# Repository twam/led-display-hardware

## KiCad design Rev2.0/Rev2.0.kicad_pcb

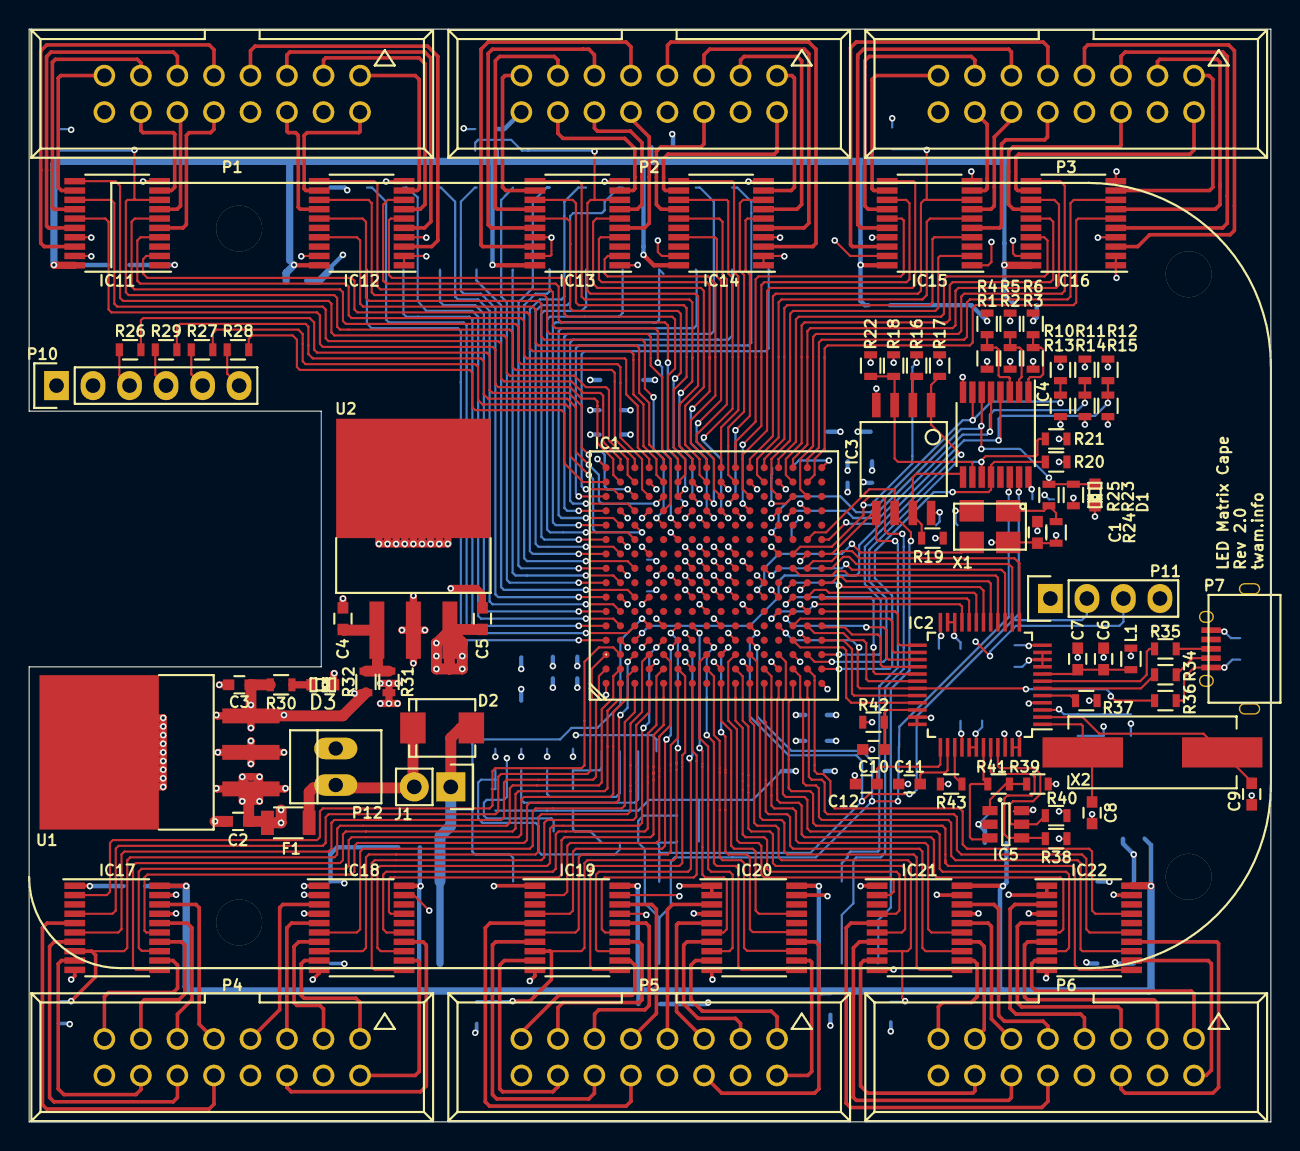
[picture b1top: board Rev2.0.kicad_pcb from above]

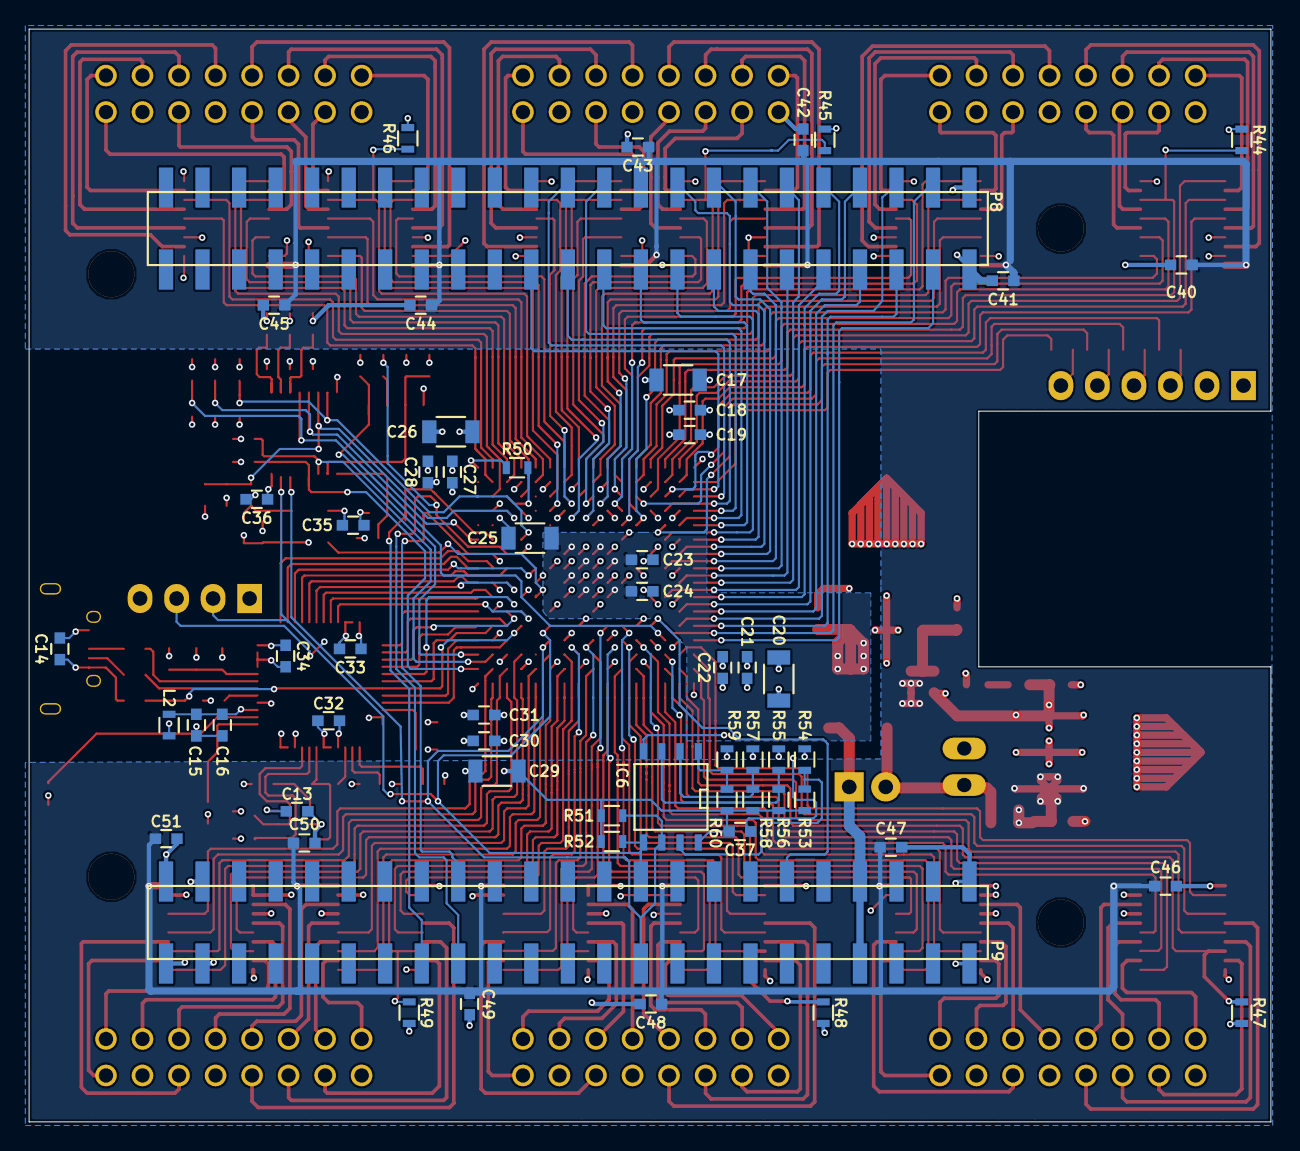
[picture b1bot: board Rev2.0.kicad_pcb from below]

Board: 4 copper layers, 86.4 x 76.0 mm, 150 parts (58 on the bottom side), 256 nets.

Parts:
C1, C10, C14: 10n; C_0603
C2, C3, C4, C5, C6, C15, C18, C21, C23, C27, C30: 4u7; C_0603
C7, C11, C12, C13, C16, C32, C33, C34, C35, C36, C37, C40, C41, C42, C43, C44, C45, C46, C47, C48, C49, C50, C51: 100n; C_0603
C8, C9: 27p; C_0603
C17, C20, C25, C26, C29: 100u; C_1206
C19, C22, C24, C28, C31: 470n; C_0603
D1, D3: LED; LED-0603
D2: DIODE; DO-214-AA
F1: FUSE; R_1206
IC1: XC6SLX25-FTG256; BGA-256
IC2: FT232H; LQFP-48_7x7mm_Pitch0.5mm
IC3: M25PE16; SO8W
IC4: PCA9534PW; TSSOP-16_4.4x5mm_Pitch0.65mm
IC5: 93LC56BT-I/OT; SOT-23-6
IC6: 24LC256; SOIC-8-N
IC11, IC12, IC13, IC14, IC15, IC16, IC17, IC18, IC19, IC20, IC21, IC22: SN74ACT244; TSSOP-20_4.4x6.5mm_Pitch0.65mm
J1: JUMPER-2; Pin_Header_Straight_1x02
L1, L2: 600R/0.5A; R_0603
MOUNTING_HOLE_3-2MM_M3, MOUNTING_HOLE_3-2MM_M3#2, MOUNTING_HOLE_3-2MM_M3#3, MOUNTING_HOLE_3-2MM_M3#4: VAL**; MOUNTING_HOLE_3-2MM_M3
P1, P2, P3, P4, P5, P6: CONN_02X08; VASCH8x2
P7: USB-MICRO-B; 47589-0001
P8: BEAGLEBONE_P8; PIN_HEADER_SMD_2x23
P9: BEAGLEBONE_P9; PIN_HEADER_SMD_2x23
P10: JTAG; Pin_Header_Straight_1x06
P11: I2C; Pin_Header_Straight_1x04
P12: POWER; PINHEAD1-2
R1, R2, R24, R38, R40: 10k N.F.; R_0603
R3: 10k N.F..; R_0603
R4, R5, R6, R10, R11, R12, R13, R14, R15, R17, R18, R19, R20, R21, R22, R25, R39, R42, R44, R45, R46, R47, R48, R49, R50, R53, R54, R55, R56, R57, R58, R59, R60: 10k; R_0603
R16, R26, R27, R28, R29: 100R; R_0603
R23, R30: 330R; R_0603
R31, R34, R35, R43: 0R; R_0603
R32: 0R N.F.; R_0603
R36: 39k; R_0603
R37: 12k/1%; R_0603
R41: 2k; R_0603
R51, R52: 4k7; R_0603
U1: MCP1826S-33; 3-DDPAK
U2: MCP1826S-12; 3-DDPAK
X1: ASFL1
X2: 12M; Crystal_HC49-SD_SMD

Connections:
+1.2V: C5.1, C23.1, C24.1, C25.1, IC1.G7, IC1.G9, IC1.H8, IC1.H10, IC1.J7, IC1.J9, IC1.K8, IC1.K10, U2.3
+3V3: C1.1, C3.1, C13.1, C17.1, C18.1, C19.1, C20.1, C21.1, C22.1, C26.1, C27.1, C28.1, C29.1, C30.1, C31.1, C32.1, C33.1, C34.1, C35.1, C36.1, C37.1, IC1.B4, IC1.B9, IC1.B13, IC1.D2, IC1.D7, IC1.D10, IC1.D15, IC1.E5, IC1.F8, IC1.F11, IC1.G4, IC1.G10, IC1.G13, IC1.H6, IC1.J2, IC1.J10, IC1.J15, IC1.K4, IC1.K13, IC1.L6, IC1.L9, IC1.N2, IC1.N7, IC1.N10, IC1.N15, IC1.R4, IC1.R8, IC1.R13, IC2.12, IC2.24, IC2.40, IC2.46, IC3.8, IC4.16, IC5.6, IC6.8, L1.2, L2.2, P10.1, P11.1, R1.1, R2.1, R3.1, R13.1, R14.1, R15.1, R17.1, R18.1, R19.1, R20.1, R21.1, R23.1, R24.1, R30.2, R32.2, R38.1, R39.1, R40.1, R42.2, R43.2, R44.2, R45.2, R46.2, R47.2, R48.2, R49.2, R51.1, R52.1, R53.1, R56.1, R58.1, R60.1, U1.3, X1.4
+5V: C2.1, C40.1, C41.1, C42.1, C43.1, C44.1, C45.1, C46.1, C47.1, C48.1, C49.1, C50.1, C51.1, F1.2, IC11.20, IC12.20, IC13.20, IC14.20, IC15.20, IC16.20, IC17.20, IC18.20, IC19.20, IC20.20, IC21.20, IC22.20, R31.2, U1.1
/BeagleBoneBlack/BBB_SYS_5V: D2.1, J1.1, P9.7, P9.8
/BeagleBoneBlack/GPMC_AD0: IC1.B14, P8.25
/BeagleBoneBlack/GPMC_AD1: IC1.A14, P8.24
/BeagleBoneBlack/GPMC_AD2: IC1.A5, P8.5
/BeagleBoneBlack/GPMC_AD3: IC1.B5, P8.6
/BeagleBoneBlack/GPMC_AD4: IC1.C13, P8.23
/BeagleBoneBlack/GPMC_AD5: IC1.A13, P8.22
/BeagleBoneBlack/GPMC_AD6: IC1.A4, P8.3
/BeagleBoneBlack/GPMC_AD7: IC1.C5, P8.4
/BeagleBoneBlack/GPMC_AD8: IC1.A12, P8.19
/BeagleBoneBlack/GPMC_AD9: IC1.C9, P8.13
/BeagleBoneBlack/GPMC_AD10: IC1.A9, P8.14
/BeagleBoneBlack/GPMC_AD11: IC1.C11, P8.17
/BeagleBoneBlack/GPMC_AD12: IC1.A8, P8.12
/BeagleBoneBlack/GPMC_AD13: IC1.B8, P8.11
/BeagleBoneBlack/GPMC_AD14: IC1.A10, P8.16
/BeagleBoneBlack/GPMC_AD15: IC1.A11, P8.15
/BeagleBoneBlack/GPMC_ADVN: IC1.A6, P8.7
/BeagleBoneBlack/GPMC_BE0N: IC1.C7, P8.9
/BeagleBoneBlack/GPMC_BE1N: IC1.D5, P9.12
/BeagleBoneBlack/GPMC_CLK: IC1.B10, P8.18
/BeagleBoneBlack/GPMC_CSN1: IC1.B12, P8.21
/BeagleBoneBlack/GPMC_OEN: IC1.B6, P8.8
/BeagleBoneBlack/GPMC_WE1N: IC1.A7, P8.10
/BeagleBoneBlack/I2C2_SCL: IC1.L4, IC4.14, IC6.6, P9.19, P11.3, R51.2
/BeagleBoneBlack/I2C2_SDA: IC1.L5, IC4.15, IC6.5, P9.20, P11.2, R52.2
/FPGA/A0_1: IC1.E15, IC11.2
/FPGA/A0_2: IC1.H16, IC13.2
/FPGA/A0_3: IC1.N14, IC15.2
/FPGA/A0_4: IC1.B3, IC17.2
/FPGA/A0_5: IC1.E3, IC19.2
/FPGA/A0_6: IC1.K3, IC21.2
/FPGA/A1_1: IC1.B15, IC11.15
/FPGA/A1_2: IC1.F14, IC13.15
/FPGA/A1_3: IC1.K16, IC15.15
/FPGA/A1_4: IC1.C3, IC17.15
/FPGA/A1_5: IC1.G1, IC19.15
/FPGA/A1_6: IC1.M2, IC21.15
/FPGA/A2_1: IC1.D16, IC11.4
/FPGA/A2_2: IC1.H13, IC13.4
/FPGA/A2_3: IC1.M16, IC15.4
/FPGA/A2_4: IC1.A3, IC17.4
/FPGA/A2_5: IC1.F4, IC19.4
/FPGA/A2_6: IC1.K1, IC21.4
/FPGA/A3_1: IC1.B16, IC11.13
/FPGA/A3_2: IC1.F15, IC13.13
/FPGA/A3_3: IC1.L13, IC15.13
/FPGA/A3_4: IC1.C2, IC17.13
/FPGA/A3_5: IC1.G3, IC19.13
/FPGA/A3_6: IC1.M1, IC21.13
/FPGA/ACBUS0: IC1.N6, IC2.21
/FPGA/ACBUS1: IC1.T6, IC2.25
/FPGA/ACBUS2: IC1.P5, IC2.26
/FPGA/ACBUS3: IC1.P6, IC2.27
/FPGA/ACBUS4: IC1.T5, IC2.28
/FPGA/ACBUS5: IC1.P7, IC2.29
/FPGA/ACBUS6: IC1.R5, IC2.30
/FPGA/ACBUS7: IC1.N5, IC2.31, R36.2
/FPGA/ACBUS8: IC1.T4, IC2.32
/FPGA/ACBUS9: IC1.P4, IC2.33
/FPGA/ADBUS0: IC1.R9, IC2.13
/FPGA/ADBUS1: IC1.T9, IC2.14
/FPGA/ADBUS2: IC1.M9, IC2.15
/FPGA/ADBUS3: IC1.P9, IC2.16
/FPGA/ADBUS4: IC1.T8, IC2.17
/FPGA/ADBUS5: IC1.P8, IC2.18
/FPGA/ADBUS6: IC1.R7, IC2.19
/FPGA/ADBUS7: IC1.T7, IC2.20
/FPGA/B0_1: IC1.E13, IC12.13
/FPGA/B0_2: IC1.J13, IC14.13
/FPGA/B0_3: IC1.P16, IC16.13
/FPGA/B0_4: IC1.E4, IC18.13
/FPGA/B0_5: IC1.H2, IC20.13
/FPGA/B0_6: IC1.P2, IC22.13
/FPGA/B1_1: IC1.E16, IC12.17
/FPGA/B1_2: IC1.H14, IC14.17
/FPGA/B1_3: IC1.N16, IC16.17
/FPGA/B1_4: IC1.E1, IC18.17
/FPGA/B1_5: IC1.J1, IC20.17
/FPGA/B1_6: IC1.R2, IC22.17
/FPGA/BLANK_1: IC1.C16, IC11.8, R44.1
/FPGA/BLANK_2: IC1.G16, IC13.8, R45.1
/FPGA/BLANK_3: IC1.L16, IC15.8, R46.1
/FPGA/BLANK_4: IC1.B2, IC17.8, R47.1
/FPGA/BLANK_5: IC1.F5, IC19.8, R48.1
/FPGA/BLANK_6: IC1.L1, IC21.8, R49.1
/FPGA/FLASH_RESET: IC3.7, IC4.9, R19.2
/FPGA/FLASH_WP: IC3.3, IC4.10, R18.2, R22.1
/FPGA/FPGA_CLK: IC1.R11, IC3.6, P9.31
/FPGA/FPGA_CLK50: IC1.M7, X1.3
/FPGA/FPGA_CS: IC1.T3, IC3.1, R17.2
/FPGA/FPGA_DONE: D1.1, IC1.P13, IC4.6, R23.2, R25.2
/FPGA/FPGA_HSWAPEN: IC1.C4, IC4.4, R12.1, R15.2
/FPGA/FPGA_INIT_B: IC1.R3, IC4.11, R21.2
/FPGA/FPGA_MISO: IC1.P10, P9.29, R16.2
/FPGA/FPGA_MODE0: IC1.T11, IC4.5, R11.1, R14.2
/FPGA/FPGA_MODE1: IC1.N11, IC4.7, R10.1, R13.2
/FPGA/FPGA_MOSI: IC1.T10, IC3.5, P9.30
/FPGA/FPGA_PROGRAM_B: IC1.T2, IC4.12, R20.2
/FPGA/G0_1: IC1.F13, IC12.8
/FPGA/G0_2: IC1.K15, IC14.8
/FPGA/G0_3: IC1.R16, IC16.8
/FPGA/G0_4: IC1.D3, IC18.8
/FPGA/G0_5: IC1.H3, IC20.8
/FPGA/G0_6: IC1.N3, IC22.8
/FPGA/G1_1: IC1.F16, IC12.6
/FPGA/G1_2: IC1.K14, IC14.6
/FPGA/G1_3: IC1.R15, IC16.6
/FPGA/G1_4: IC1.C1, IC18.6
/FPGA/G1_5: IC1.G5, IC20.6
/FPGA/G1_6: IC1.N1, IC22.6
/FPGA/LATCH_1: IC1.C15, IC11.11
/FPGA/LATCH_2: IC1.G14, IC13.11
/FPGA/LATCH_3: IC1.L14, IC15.11
/FPGA/LATCH_4: IC1.B1, IC17.11
/FPGA/LATCH_5: IC1.F2, IC19.11
/FPGA/LATCH_6: IC1.L3, IC21.11
/FPGA/R0_1: IC1.F12, IC12.11
/FPGA/R0_2: IC1.J16, IC14.11
/FPGA/R0_3: IC1.R14, IC16.11
/FPGA/R0_4: IC1.D1, IC18.11
/FPGA/R0_5: IC1.H4, IC20.11
/FPGA/R0_6: IC1.P1, IC22.11
/FPGA/R1_1: IC1.E12, IC12.15
/FPGA/R1_2: IC1.J14, IC14.15
/FPGA/R1_3: IC1.P15, IC16.15
/FPGA/R1_4: IC1.E2, IC18.15
/FPGA/R1_5: IC1.J3, IC20.15
/FPGA/R1_6: IC1.R1, IC22.15
/FPGA/SCLK_1: IC1.D14, IC11.6
/FPGA/SCLK_2: IC1.H15, IC13.6
/FPGA/SCLK_3: IC1.M15, IC15.6
/FPGA/SCLK_4: IC1.A2, IC17.6
/FPGA/SCLK_5: IC1.F1, IC19.6
/FPGA/SCLK_6: IC1.K2, IC21.6
/FPGA/TCK: IC1.C14, R26.2
/FPGA/TDI: IC1.C12, R27.2
/FPGA/TDO: IC1.E14, R29.2
/FPGA/TMS: IC1.A15, R28.2
/Outputs/A0_1_: IC11.18, P1.9
/Outputs/A0_2_: IC13.18, P2.9
/Outputs/A0_3_: IC15.18, P3.9
/Outputs/A0_4_: IC17.18, P4.9
/Outputs/A0_5_: IC19.18, P5.9
/Outputs/A0_6_: IC21.18, P6.9
/Outputs/A1_1_: IC11.5, P1.10
/Outputs/A1_2_: IC13.5, P2.10
/Outputs/A1_3_: IC15.5, P3.10
/Outputs/A1_4_: IC17.5, P4.10
/Outputs/A1_5_: IC19.5, P5.10
/Outputs/A1_6_: IC21.5, P6.10
/Outputs/A2_1_: IC11.16, P1.11
/Outputs/A2_2_: IC13.16, P2.11
/Outputs/A2_3_: IC15.16, P3.11
/Outputs/A2_4_: IC17.16, P4.11
/Outputs/A2_5_: IC19.16, P5.11
/Outputs/A2_6_: IC21.16, P6.11
/Outputs/A3_1_: IC11.7, P1.12
/Outputs/A3_2_: IC13.7, P2.12
/Outputs/A3_3_: IC15.7, P3.12
/Outputs/A3_4_: IC17.7, P4.12
/Outputs/A3_5_: IC19.7, P5.12
/Outputs/A3_6_: IC21.7, P6.12
/Outputs/B0_1_: IC12.7, P1.3
/Outputs/B0_2_: IC14.7, P2.3
/Outputs/B0_3_: IC16.7, P3.3
/Outputs/B0_4_: IC18.7, P4.3
/Outputs/B0_5_: IC20.7, P5.3
/Outputs/B0_6_: IC22.7, P6.3
/Outputs/B1_1_: IC12.3, P1.7
/Outputs/B1_2_: IC14.3, P2.7
/Outputs/B1_3_: IC16.3, P3.7
/Outputs/B1_4_: IC18.3, P4.7
/Outputs/B1_5_: IC20.3, P5.7
/Outputs/B1_6_: IC22.3, P6.7
/Outputs/BLANK_1_: IC11.12, P1.15
/Outputs/BLANK_2_: IC13.12, P2.15
/Outputs/BLANK_3_: IC15.12, P3.15
/Outputs/BLANK_4_: IC17.12, P4.15
/Outputs/BLANK_5_: IC19.12, P5.15
/Outputs/BLANK_6_: IC21.12, P6.15
/Outputs/G0_1_: IC12.12, P1.2
/Outputs/G0_2_: IC14.12, P2.2
/Outputs/G0_3_: IC16.12, P3.2
/Outputs/G0_4_: IC18.12, P4.2
/Outputs/G0_5_: IC20.12, P5.2
/Outputs/G0_6_: IC22.12, P6.2
/Outputs/G1_1_: IC12.14, P1.6
/Outputs/G1_2_: IC14.14, P2.6
/Outputs/G1_3_: IC16.14, P3.6
/Outputs/G1_4_: IC18.14, P4.6
/Outputs/G1_5_: IC20.14, P5.6
/Outputs/G1_6_: IC22.14, P6.6
/Outputs/LATCH_1_: IC11.9, P1.14
/Outputs/LATCH_2_: IC13.9, P2.14
/Outputs/LATCH_3_: IC15.9, P3.14
/Outputs/LATCH_4_: IC17.9, P4.14
/Outputs/LATCH_5_: IC19.9, P5.14
/Outputs/LATCH_6_: IC21.9, P6.14
/Outputs/R0_1_: IC12.9, P1.1
/Outputs/R0_2_: IC14.9, P2.1
/Outputs/R0_3_: IC16.9, P3.1
/Outputs/R0_4_: IC18.9, P4.1
/Outputs/R0_5_: IC20.9, P5.1
/Outputs/R0_6_: IC22.9, P6.1
/Outputs/R1_1_: IC12.5, P1.5
/Outputs/R1_2_: IC14.5, P2.5
/Outputs/R1_3_: IC16.5, P3.5
/Outputs/R1_4_: IC18.5, P4.5
/Outputs/R1_5_: IC20.5, P5.5
/Outputs/R1_6_: IC22.5, P6.5
/Outputs/SCLK_1_: IC11.14, P1.13
/Outputs/SCLK_2_: IC13.14, P2.13
/Outputs/SCLK_3_: IC15.14, P3.13
/Outputs/SCLK_4_: IC17.14, P4.13
/Outputs/SCLK_5_: IC19.14, P5.13
/Outputs/SCLK_6_: IC21.14, P6.13
/USB/EECLK: IC2.44, IC5.4, R38.2
/USB/EECS: IC2.45, IC5.5, R40.2
/USB/EEDATA: IC2.43, IC5.3, R41.1
/USB/USB_DM: IC2.6, R34.2
/USB/USB_DP: IC2.7, R35.2
/USB/USB_RESET: C10.1, IC2.34, R42.1
/USB/USB_VBUS: C14.1, P7.1, R36.1
GND: C1.2, C2.2, C3.2, C4.2, C5.2, C6.2, C7.2, C8.2, C9.2, C10.2, C11.2, C12.2, C13.2, C14.2, C15.2, C16.2, C17.2, C18.2, C19.2, C20.2, C21.2, C22.2, C23.2, C24.2, C25.2, C26.2, C27.2, C28.2, C29.2, C30.2, C31.2, C32.2, C33.2, C34.2, C35.2, C36.2, C37.2, C40.2, C41.2, C42.2, C43.2, C44.2, C45.2, C46.2, C47.2, C48.2, C49.2, C50.2, C51.2, D1.2, D3.2, IC1.A1, IC1.A16, IC1.B7, IC1.B11, IC1.D4, IC1.D13, IC1.E9, IC1.G2, IC1.G8, IC1.G15, IC1.H7, IC1.H9, IC1.H12, IC1.J5, IC1.J8, IC1.K7, IC1.K9, IC1.L2, IC1.L15, IC1.M8, IC1.N13, IC1.P3, IC1.R6, IC1.R10, IC1.T1, IC1.T16, IC2.4, IC2.9, IC2.10, IC2.11, IC2.22, IC2.23, IC2.35, IC2.36, IC2.41, IC2.42, IC2.47, IC2.48, IC3.4, IC4.8, IC5.2, IC6.4, IC11.1, IC11.10, IC11.17, IC11.19, IC12.1, IC12.2, IC12.4, IC12.10, IC12.19, IC13.1, IC13.10, IC13.17, IC13.19, IC14.1, IC14.2, IC14.4, IC14.10, IC14.19, IC15.1, IC15.10, IC15.17, IC15.19, IC16.1, IC16.2, IC16.4, IC16.10, IC16.19, IC17.1, IC17.10, IC17.17, IC17.19, IC18.1, IC18.2, IC18.4, IC18.10, IC18.19, IC19.1, IC19.10, IC19.17, IC19.19, IC20.1, IC20.2, IC20.4, IC20.10, IC20.19, IC21.1, IC21.10, IC21.17, IC21.19, IC22.1, IC22.2, IC22.4, IC22.10, IC22.19, P1.4, P1.8, P1.16, P2.4, P2.8, P2.16, P3.4, P3.8, P3.16, P4.4, P4.8, P4.16, P5.4, P5.8, P5.16, P6.4, P6.8, P6.16, P7.5, P7.6, P7.7, P7.8, P7.9, P8.1, P8.2, P9.1, P9.2, P9.43, P9.44, P9.45, P9.46, P10.2, P11.4, P12.2, R4.2, R5.2, R6.2, R10.2, R11.2, R12.2, R22.2, R37.2, R50.2, R54.2, R55.2, R57.2, R59.2, U1.2, U1.4, U2.2, U2.4, X1.2
unnamed: C4.1, R31.1, R32.1, U2.1
unnamed: C6.1, C7.1, IC2.8, L1.1
unnamed: C8.1, IC2.1, X2.1
unnamed: C9.1, IC2.2, X2.2
unnamed: C11.1, IC2.38
unnamed: C12.1, IC2.37
unnamed: C15.1, C16.1, IC2.3, L2.1
unnamed: D2.2, F1.1, J1.2, P12.1
unnamed: D3.1, R30.1
unnamed: IC1.P14, R50.1
unnamed: IC2.5, R37.1
unnamed: IC2.39, R43.1
unnamed: IC3.2, R16.1
unnamed: IC4.1, R3.2, R6.1
unnamed: IC4.2, R2.2, R5.1
unnamed: IC4.3, R1.2, R4.1
unnamed: IC5.1, R39.2, R41.2
unnamed: IC6.1, R59.1, R60.2
unnamed: IC6.2, R57.1, R58.2
unnamed: IC6.3, R55.1, R56.2
unnamed: IC6.7, R53.2, R54.1
unnamed: P7.2, R34.1
unnamed: P7.3, R35.1
unnamed: P10.3, R26.1
unnamed: P10.4, R29.1
unnamed: P10.5, R27.1
unnamed: P10.6, R28.1
unnamed: R24.2, R25.1, X1.1

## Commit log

2015-06-09 Rev 1.0 board
2015-06-09 Rev 2.0 board
